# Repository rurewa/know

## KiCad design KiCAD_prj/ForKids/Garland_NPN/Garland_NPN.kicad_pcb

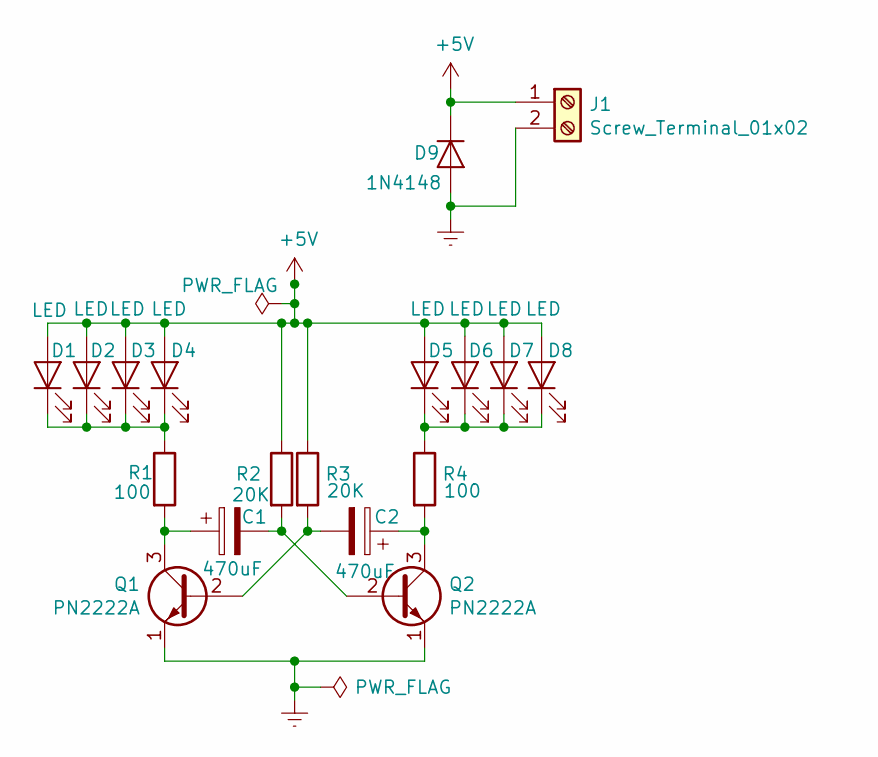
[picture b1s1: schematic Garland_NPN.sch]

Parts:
C1, C2: 470uF; CP_Radial_D8.0mm_P3.50mm
D1, D2, D3, D4, D5, D6, D7, D8: LED; LED_D3.0mm
D9: 1N4148; D_DO-35_SOD27_P7.62mm_Horizontal
J1: Screw_Terminal_01x02; PhoenixContact_MCV_1,5_2-G-3.5_1x02_P3.50mm_Vertical
Q1, Q2: PN2222A; TO-92_Inline_Wide
R1, R4: 100; R_Axial_DIN0207_L6.3mm_D2.5mm_P7.62mm_Horizontal
R2, R3: 20K; R_Axial_DIN0207_L6.3mm_D2.5mm_P7.62mm_Horizontal

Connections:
+5V: D1.2 (A), D2.2 (A), D3.2 (A), D4.2 (A), D5.2 (A), D6.2 (A), D7.2 (A), D8.2 (A), D9.1 (K), J1.1, R2.1, R3.1
Earth: D9.2 (A), J1.2, Q1.1 (E), Q2.1 (E)
unnamed: C1.1, Q1.3 (C), R1.2
unnamed: C1.2, Q2.2 (B), R2.2
unnamed: C2.1, Q2.3 (C), R4.2
unnamed: C2.2, Q1.2 (B), R3.2
unnamed: D1.1 (K), D2.1 (K), D3.1 (K), D4.1 (K), R1.1
unnamed: D5.1 (K), D6.1 (K), D7.1 (K), D8.1 (K), R4.1

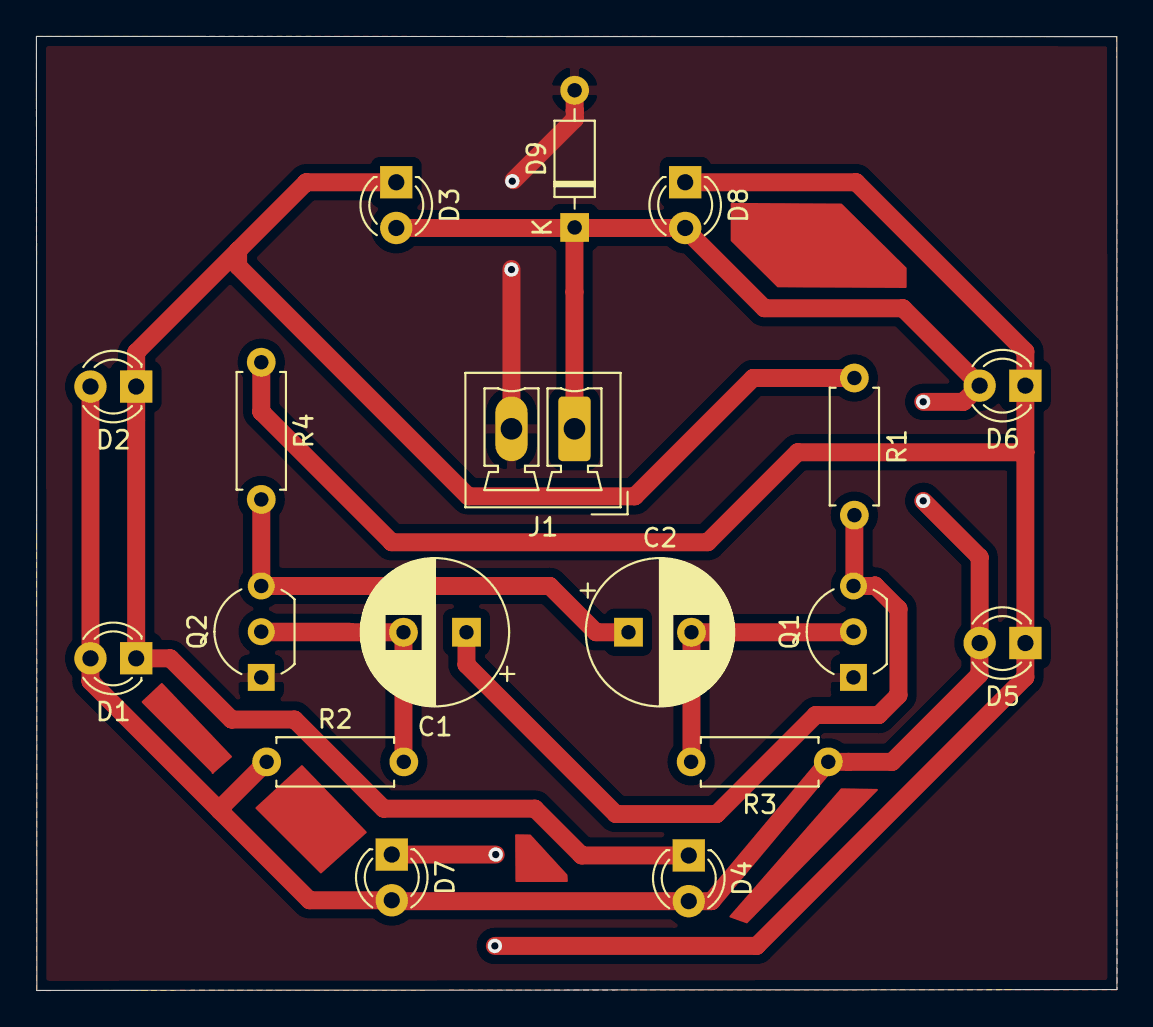
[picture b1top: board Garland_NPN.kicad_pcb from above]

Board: 2 copper layers, 60.0 x 53.0 mm, 18 parts (0 on the bottom side), 8 nets.

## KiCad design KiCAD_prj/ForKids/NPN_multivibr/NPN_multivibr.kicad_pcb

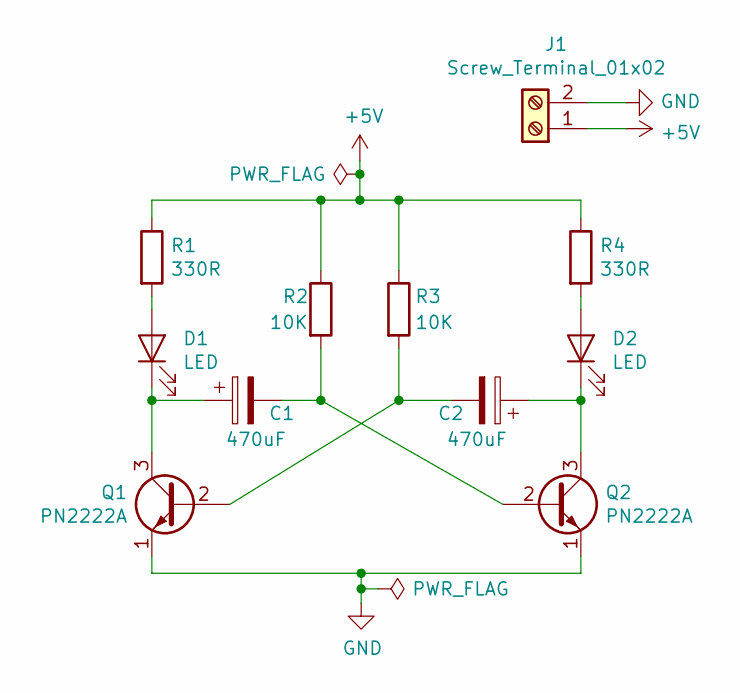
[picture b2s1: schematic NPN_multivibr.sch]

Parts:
C1, C2: 470uF; CP_Radial_D8.0mm_P5.00mm
D1, D2: LED; LED_D3.0mm
J1: Screw_Terminal_01x02; PhoenixContact_MCV_1,5_2-G-3.5_1x02_P3.50mm_Vertical
Q1, Q2: PN2222A; TO-92L_Wide
R1, R4: 330R; R_Axial_DIN0207_L6.3mm_D2.5mm_P7.62mm_Horizontal
R2, R3: 10K; R_Axial_DIN0207_L6.3mm_D2.5mm_P7.62mm_Horizontal

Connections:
+5V: J1.1, R1.1, R2.1, R3.1, R4.1
GND: J1.2, Q1.1 (E), Q2.1 (E)
unnamed: C1.1, D1.1 (K), Q1.3 (C)
unnamed: C1.2, Q2.2 (B), R2.2
unnamed: C2.1, D2.1 (K), Q2.3 (C)
unnamed: C2.2, Q1.2 (B), R3.2
unnamed: D1.2 (A), R1.2
unnamed: D2.2 (A), R4.2

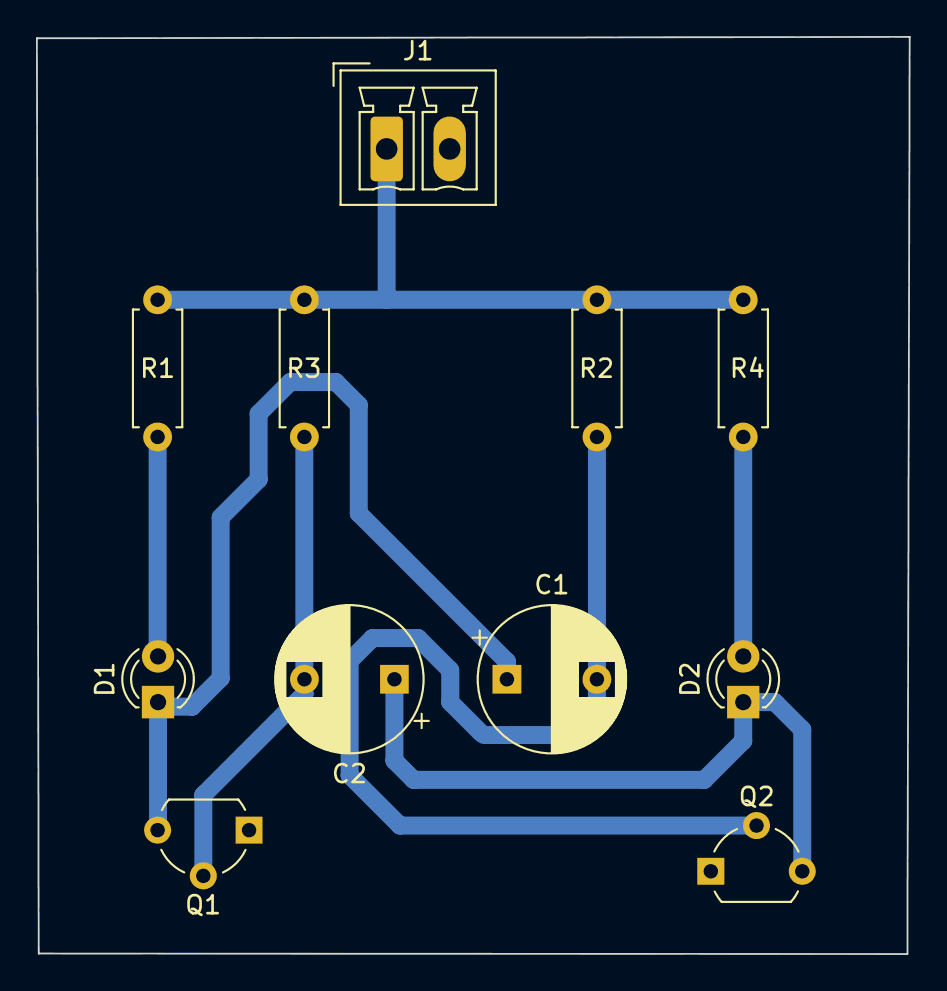
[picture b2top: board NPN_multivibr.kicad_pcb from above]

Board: 2 copper layers, 48.5 x 51.0 mm, 11 parts (0 on the bottom side), 8 nets.

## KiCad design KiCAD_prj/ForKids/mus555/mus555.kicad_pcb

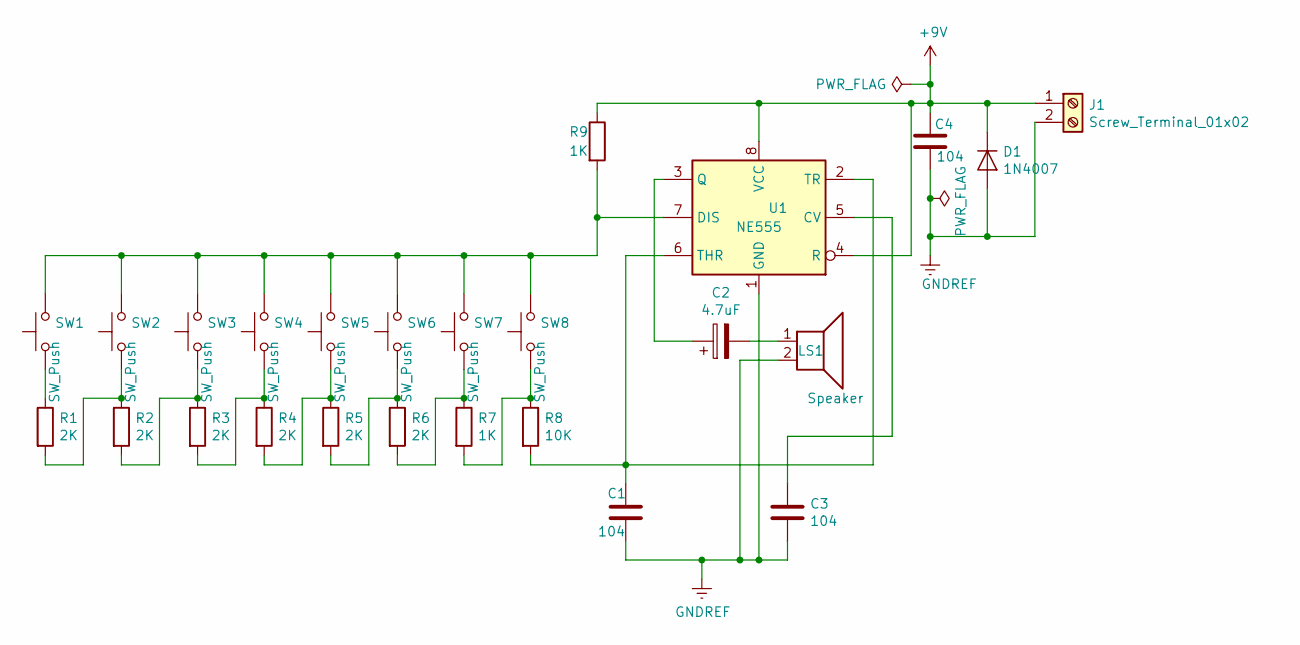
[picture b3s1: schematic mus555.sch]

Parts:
C1, C3, C4: 104; C_Disc_D4.7mm_W2.5mm_P5.00mm
C2: 4.7uF; CP_Radial_D8.0mm_P3.50mm
D1: 1N4007; D_DO-35_SOD27_P5.08mm_Vertical_AnodeUp
J1: Screw_Terminal_01x02; PhoenixContact_MCV_1,5_2-G-3.5_1x02_P3.50mm_Vertical
LS1: Speaker; PhoenixContact_MCV_1,5_2-G-3.5_1x02_P3.50mm_Vertical
R1, R2, R3, R4, R5, R6: 2K; R_Axial_DIN0207_L6.3mm_D2.5mm_P7.62mm_Horizontal
R7, R9: 1K; R_Axial_DIN0207_L6.3mm_D2.5mm_P7.62mm_Horizontal
R8: 10K; R_Axial_DIN0207_L6.3mm_D2.5mm_P7.62mm_Horizontal
SW1, SW2, SW3, SW4, SW5, SW6, SW7, SW8: SW_Push; SolderWirePad_1x02_P3.81mm_Drill0.8mm
U1: NE555; DIP-8_W7.62mm_LongPads

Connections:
+9V: C4.1, D1.1 (K), J1.1, R9.1, U1.4 (R), U1.8 (VCC)
GNDREF: C1.2, C3.2, C4.2, D1.2 (A), J1.2, LS1.2, U1.1 (GND)
unnamed: C1.1, R8.2, U1.2 (TR), U1.6 (THR)
unnamed: C2.1, U1.3 (Q)
unnamed: C2.2, LS1.1
unnamed: C3.1, U1.5 (CV)
unnamed: R1.1, SW1.1
unnamed: R1.2, R2.1, SW2.1
unnamed: R2.2, R3.1, SW3.1
unnamed: R3.2, R4.1, SW4.1
unnamed: R4.2, R5.1, SW5.1
unnamed: R5.2, R6.1, SW6.1
unnamed: R6.2, R7.1, SW7.1
unnamed: R7.2, R8.1, SW8.1
unnamed: R9.2, SW1.2, SW2.2, SW3.2, SW4.2, SW5.2, SW6.2, SW7.2, SW8.2, U1.7 (DIS)

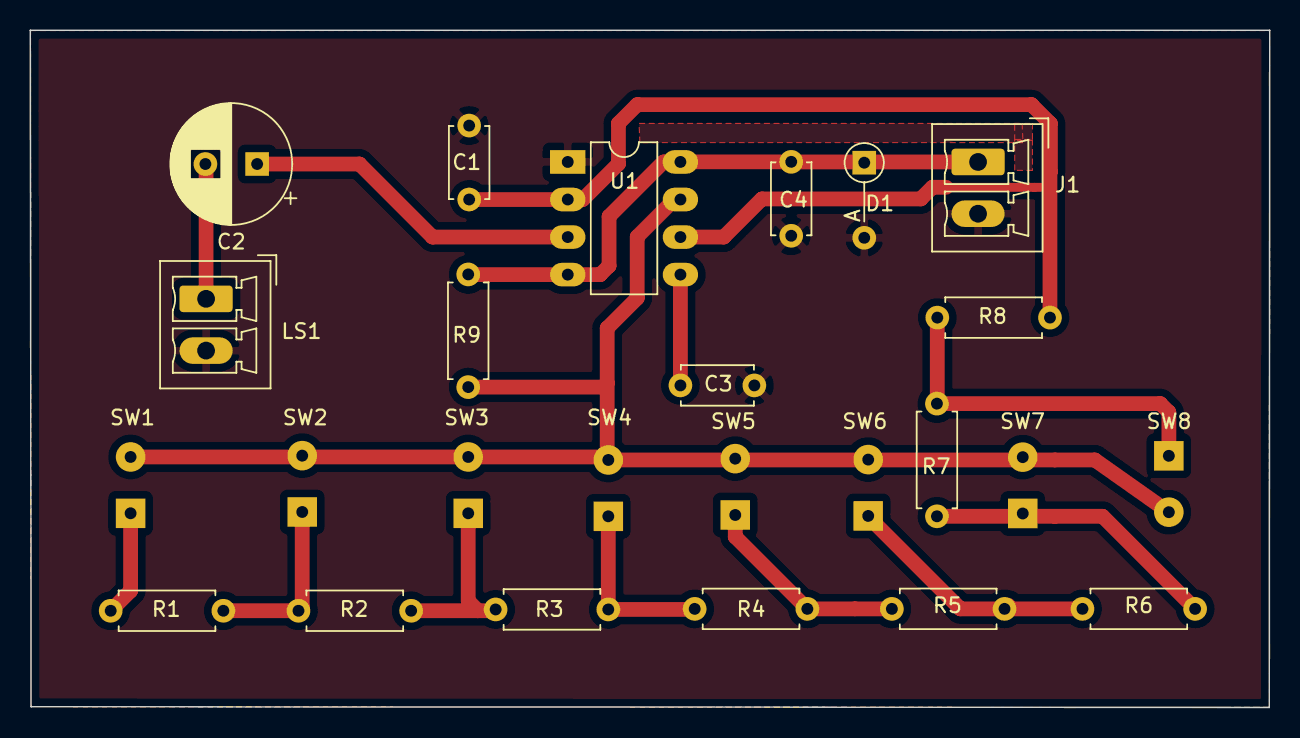
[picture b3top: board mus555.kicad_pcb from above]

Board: 2 copper layers, 83.8 x 45.8 mm, 25 parts (0 on the bottom side), 15 nets.
